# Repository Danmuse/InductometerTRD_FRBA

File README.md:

<!-- Official repository: https://github.com/Danmuse/InductometerTRD_FRBA -->
<!--
<details>
  <summary><strong><span>&#160;</span>References</strong></summary>
  <ul>
    <span>&#10038;</span> [STM32F103C8Tx interesting projects](https://github.com/CaliBeta).<br>
    <span>&#10038;</span> [Generate sinusiodal signal with Pulse-Width Modulation](https://www.youtube.com/watch?v=9wfItbD-dHI).<br>
    <span>&#10038;</span> [STM32 Blue-pill VS Arduino NANO](https://www.youtube.com/watch?v=mdxmfjVhEus).<br>
    <span>&#10038;</span> [Arduino IDE with ARM Cortex-M3 STM32](https://github.com/stm32duino/Arduino_Core_STM32/wiki/API).<br>
    <span>&#10038;</span> [Analog/digital filters designer](https://www.micromodeler.com/dsp/).<br>
    <span>&#10038;</span> [Debug the STM32 using the Arduino IDE](https://community.st.com/t5/stm32-mcus/how-to-program-and-debug-the-stm32-using-the-arduino-ide/ta-p/608514).<br>
    <span>&#10038;</span> [DC-DC Symmetrical Boost Source with MT3608](https://www.youtube.com/watch?v=GvgKwTZ24lw).<br>
    <span>&#10038;</span> [Function generator using AD9833 chipset](https://www.allaboutcircuits.com/projects/how-to-DIY-waveform-generator-analog-devices-ad9833-ATmega328p/).<br>
  </ul>
</details>
-->

## 📕️ __Overview__

The **Inductometer** project with autoranging aims to create a device to measure inductance and calculate the quality factor of any inductor from the resonance frequency of the circuit. This meter is ideal for educational, research and electronic design applications.

### 🔌️ __Hardware & Setup__

- [ ] [Identification of the sensors, modules and controllers used.](https://github.com/Danmuse/InductometerTRD_FRBA/issues/1) `DDM ~ 14`
<details>
  <summary><strong><span>&#160;</span>Electronic components</strong></summary>
  <ul>
    <span>&#10038;</span> <b>STM32F103C8T6 Blue-pill board</b>.<br>
    <span>&#10038;</span> <b>18650</b> Rechargeable Li-ion battery (3.65V/2.6A).<br>
    <span>&#10038;</span> <b>TP4056</b> Charging module for 3.7V/1A Li-ion battery.<br>
    <span>&#10038;</span> <b>AD9833</b> DDS Sinusoidal/triangular/square signal generator (1Hz ~ 12MHz).<br>
    <span>&#10038;</span> <b>MT3608</b> Step up (2V ~ 28V/2A).<br>
    <span>&#10038;</span> <b>INA219</b> Current/voltage sensor (500mV ~ 26V/3.2A).<br>
    <span>&#10038;</span> <b>X9C103S</b> 10KΩ digital potentiometer.<br>
    <span>&#10038;</span> <b>OPA564</b> Potencial operational amplifier.<br>
    <span>&#10038;</span> <b>TL082CD</b> and <b>TL081CD</b> Operational amplifiers.<br>
    <span>&#10038;</span> <b>NTF6P02T3G</b> MOSFET P-Channel.<br>
    <!-- <span>&#10038;</span> <b>100Ω</b> 1/4W and <b>220Ω</b> 1/4W Resistors.<br>
    <span>&#10038;</span> <b>TLV3501AID</b> High speed comparator with shutdown.<br>
    <span>&#10038;</span> Mx471 Current/Voltage sensor ~ Maximum 3A/3-36V. (Q-meter)<br>
    <span>&#10038;</span> ACS712T-5A Current sensor ~ Maximum 5A. (Q-meter)<br>
    <span>&#10038;</span> FZ0430 Voltage sensor ~ Maximum 25V. (Q-meter)<br> -->
    <span>&#10038;</span> Capacitor bank with different types.<br>
    <span>&#10038;</span> <b>KY-040</b> Incremental rotary encoder.<br>
    <span>&#10038;</span> IPS HD TFT <b>ST7789</b>.<br>
    <span>&#10038;</span> Slide power switch.<br>
    <!-- <span>&#10038;</span> EEPROM Memory FM24C16U 16KB. (Optional)<br> -->
  </ul>
</details>

- [ ] [Hardware installations and cabinet design.](https://github.com/Danmuse/InductometerTRD_FRBA/issues/2) `DDM ~ 0`
- [ ] [Development board (Schematic and PCB).](https://github.com/Danmuse/InductometerTRD_FRBA/issues/3) `DDM ~ 17`
- [ ] [Circuit simulations with LTSpice.](https://github.com/Danmuse/InductometerTRD_FRBA/issues/10) `DDM ~ 32`

### 👨‍💻️ __Firmware & Software__

- [ ] [Achieving connectivity between sensors and modules with the microcontroller.](https://github.com/Danmuse/InductometerTRD_FRBA/issues/4) `DDM ~ 123` `MSS ~ 0`

### 📚️ __Documentation & Doxygen__

- [ ] [Doxygen v1.9.6 implementation for code documentation.](https://github.com/Danmuse/InductometerTRD_FRBA/issues/5) `DDM ~ 0`
- [x] [Presentation of the project idea.](https://github.com/Danmuse/InductometerTRD_FRBA/issues/6) `DDM ~ 4.5` `MSS ~ 1`
- [ ] [Comprehensive and extensive project report.](https://github.com/Danmuse/InductometerTRD_FRBA/issues/7) `DDM ~ 0.5` `MSS ~ 0`
- [ ] [Illustrations of the experience and trials.](https://github.com/Danmuse/InductometerTRD_FRBA/issues/8) `DDM ~ 6`
- [ ] [Load component datasheet.](https://github.com/Danmuse/InductometerTRD_FRBA/issues/9) `DDM ~ 7`

---

## 🌟️ __Contributing__

General Firmware Developers: __@Danmuse__  
General Hardware Developers: __@Danmuse__ ~ __@msanchezsosa__  
Documentation Managers: __@Danmuse__ ~ __@msanchezsosa__   
Doxygen Editor: __@Danmuse__  

<br>

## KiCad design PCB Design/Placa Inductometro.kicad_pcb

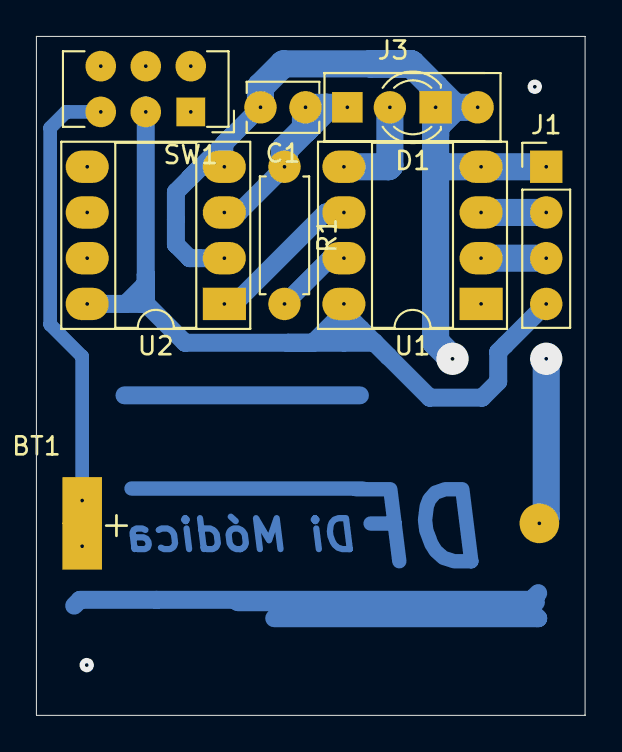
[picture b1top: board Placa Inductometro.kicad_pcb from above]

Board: 2 copper layers, 30.5 x 37.7 mm, 9 parts (0 on the bottom side), 9 nets.

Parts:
BT1: CR2032; BatteryHolder_Keystone_103_1x20mm
C1: 1u; C_Disc_D3.8mm_W2.6mm_P2.50mm
D1: LED; LED_D3.0mm
J1: Display; PinHeader_1x04_P2.54mm_Vertical
J3: Lx; TerminalBlock_bornier-2_P5.08mm
R1: 220; R_Axial_DIN0207_L6.3mm_D2.5mm_P7.62mm_Horizontal
SW1: SW_DPDT_x2; SW_CuK_JS202011AQN_DPDT_Angled
U1: ATtiny85-20PU; DIP-8_W7.62mm_Socket_LongPads
U2: LM393; DIP-8_W7.62mm_Socket_LongPads

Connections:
unnamed: BT1.1, SW1.3
unnamed: BT1.2, C1.2, D1.1, J1.1, J3.2, U1.4, U2.2, U2.4
unnamed: C1.1, J3.1, R1.1, U2.3
unnamed: D1.2, U1.5
unnamed: J1.4, SW1.2, U1.8, U2.8
unnamed: J1.2, U1.3
unnamed: J1.3, U1.2
unnamed: R1.2, U1.7
unnamed: U1.6, U2.1

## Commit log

2024-05-26 Release the version v1.0 of the Inductometer project without autoranging
2024-05-26 Add README file
2024-05-26 Add useful templates to prepare the documentation of the project ~ Issue related #6
2024-05-26 Add datasheets of some modules and controllers used ~ Issue related #9
2024-05-27 Add LTspice simulations files
2024-06-05 Complete the initial project idea ~ Issue related #6
2024-06-22 Achieving connectivity with the ST7789 TFT ~ Issue related #4
2024-07-07 Add some images to use on this project's presentation ~ Issue related #8
2024-07-07 Add some module and component datasheets ~ Issue related #9
2024-07-07 Implement functions to control the ST7789 module and attach some examples ~ Issue related #4
2024-07-17 Print images with .bin extension files on the TFT ST7789 using SD card ~ Issue related #4
2024-07-18 Add several images about the corrections of the modules ~ Issue related #8
2024-07-18 Optimize the image printing process corresponding to the TFT ST7789 ~ Issue related #4
2024-07-22 Add more images to use in the presentations of the project ~ Issue related #8
2024-07-22 Incorporate state machine and menu control with the incremental encoder ~ Issue related #4
2024-07-25 Complete the user interface for the signal generator ~ Issue related #4
2024-07-26 Change the menu background image ~ Issue related #8
2024-07-26 Project restructuring, DMA analysis and adding warnings ~ Issue related #4
2024-07-27 Achieve control of AD9833 peripheral ~ Issue related #4
2024-07-28 Include the MCP4725Ax library ~ Issue related #4
2024-08-04 Generate simulation of the symmetrical source circuit and amplification stage for the generator signal response ~ Issue related #10
2024-08-26 Fix the legends and time limit of the main simulation ~ Issue related #10
2024-08-26 Update some components' datasheets according to hardware limitations ~ Issue related #9
2024-08-26 Reorganize the images collected during the developing ~ Issue related #8
2024-08-26 Include more template libraries and generate a scope to test DDS functions ~ Issue related #4
2024-08-26 Beginning of the project schematic ~ Issue related #3
2024-09-25 Suppression of the current surge produced by the DC/DC boost transient. Simulation subcircuits included ~ Issue related #10
2024-09-25 Trying to correct the inconsistency when configuring DDS. Test scripts included ~ Issue related #4
2024-09-30 Fix the signal generation during configuration and implement the MCP4725Ax library ~ Issue related #4
2024-10-10 Include LM6172 and OPA380 OPAMPs to simulate their behaviors ~ Issue related #10
2024-10-10 Optimize some code instructions ~ Issue related #4
